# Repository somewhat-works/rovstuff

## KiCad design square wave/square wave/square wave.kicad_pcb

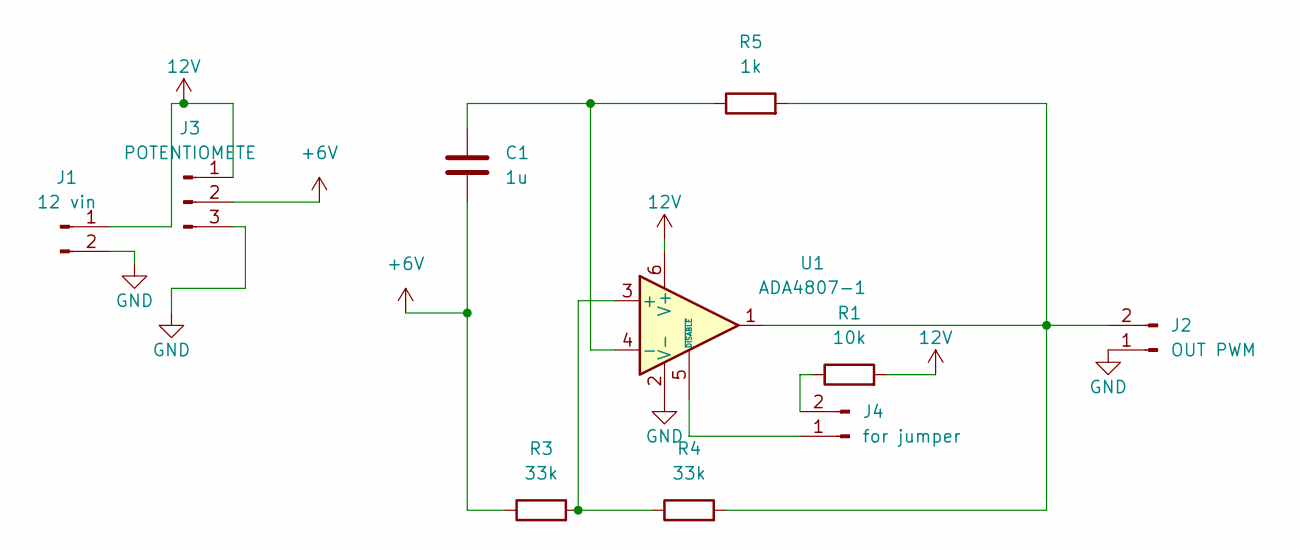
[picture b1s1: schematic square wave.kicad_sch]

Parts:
C1: 1u; C_0805_2012Metric
J1: 12 vin; PinHeader_1x02_P2.54mm_Vertical
J2: OUT PWM; PinHeader_1x02_P2.54mm_Vertical
J3: POTENTIOMETE; PinSocket_1x03_P2.54mm_Vertical
J4: for jumper; PinHeader_1x02_P2.54mm_Vertical
R1: 10k; R_0805_2012Metric
R3, R4: 33k; R_0805_2012Metric
R5: 1k; R_Axial_DIN0411_L9.9mm_D3.6mm_P15.24mm_Horizontal
U1: ADA4807-1; SOT-23-6

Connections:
12V: J1.1, J3.1, R1.2, U1.6 (V+)
+6V: C1.2, J3.2, R3.1
GND: J1.2, J2.1, J3.3, U1.2 (V-)
unnamed: J2.2, R4.2, R5.2, U1.1
unnamed: J4.1, U1.5 (~DISABLE)
unnamed: J4.2, R1.1
unnamed: R3.2, R4.1, U1.3 (+)
unnamed: C1.1, R5.1, U1.4 (-)

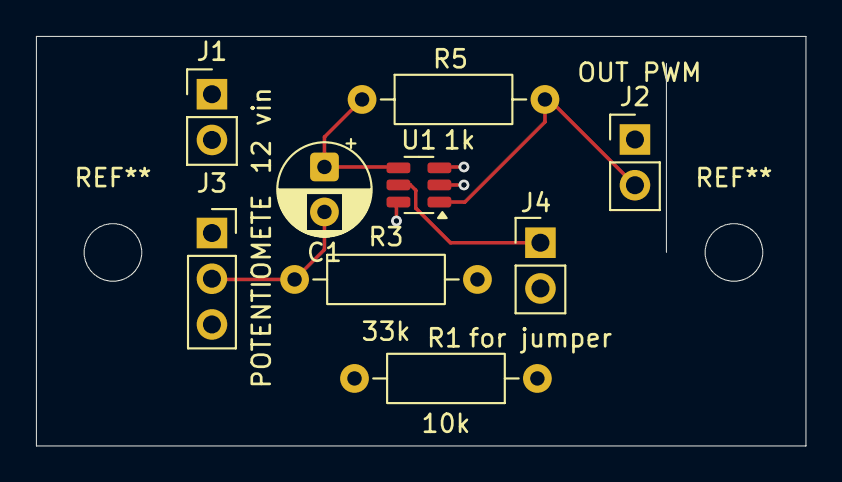
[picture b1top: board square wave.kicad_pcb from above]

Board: 4 copper layers, 42.8 x 22.8 mm, 9 parts (0 on the bottom side), 8 nets.

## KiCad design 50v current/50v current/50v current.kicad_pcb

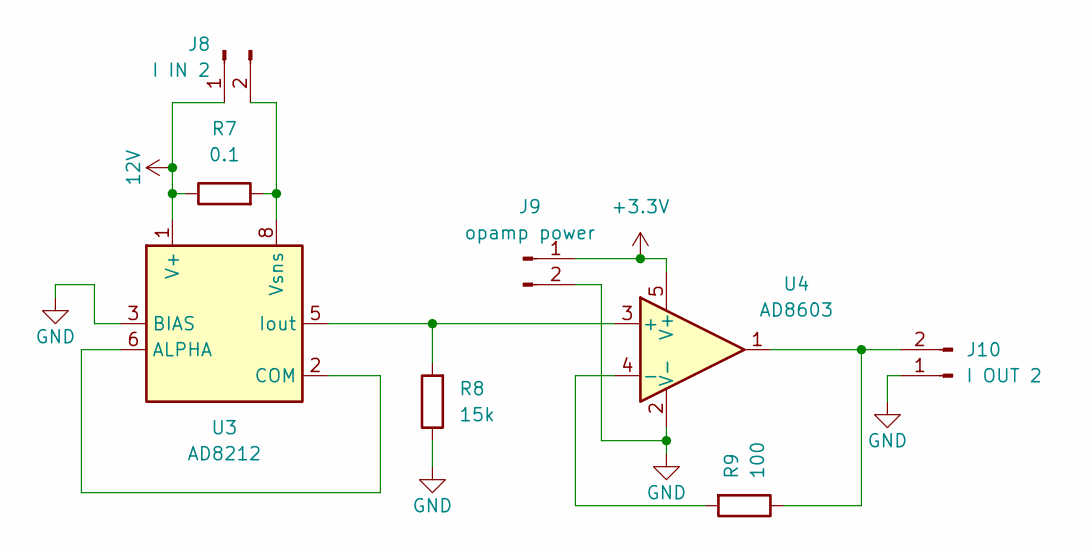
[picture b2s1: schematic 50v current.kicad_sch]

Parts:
J8: I IN 2; PinHeader_1x02_P2.54mm_Vertical
J9: opamp power; PinHeader_1x02_P2.54mm_Vertical
J10: I OUT 2; PinHeader_1x02_P2.54mm_Vertical
R7: 0.1; R_Axial_DIN0204_L3.6mm_D1.6mm_P5.08mm_Horizontal
R8: 15k; R_0805_2012Metric
R9: 100; R_0805_2012Metric
U3: AD8212; MSOP-8_3x3mm_P0.65mm
U4: AD8603; TSOT-23-5

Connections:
12V: J8.1, R7.1, U3.1 (V+)
+3.3V: J9.1, U4.5 (V+)
GND: J9.2, J10.1, R8.1, U3.3 (BIAS), U4.2 (V-)
unnamed: J8.2, R7.2, U3.8 (Vsns)
unnamed: J10.2, R9.1, U4.1
unnamed: U3.2 (COM), U3.6 (ALPHA)
unnamed: R8.2, U3.5 (Iout), U4.3 (+)
unnamed: R9.2, U4.4 (-)

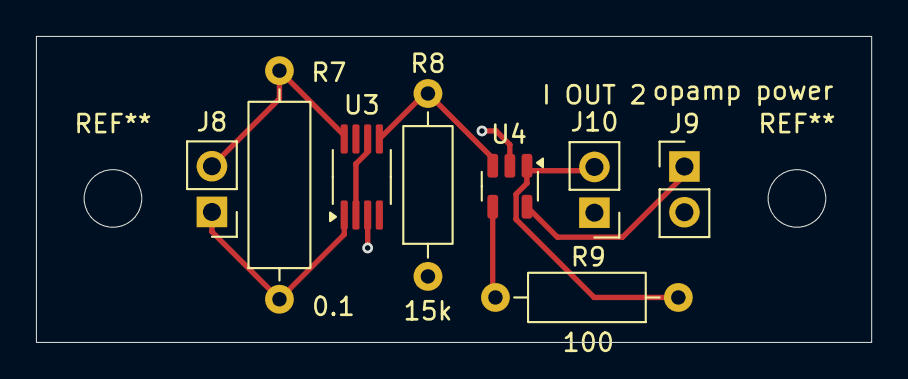
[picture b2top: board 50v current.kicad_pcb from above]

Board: 2 copper layers, 46.4 x 17.0 mm, 8 parts (0 on the bottom side), 8 nets.

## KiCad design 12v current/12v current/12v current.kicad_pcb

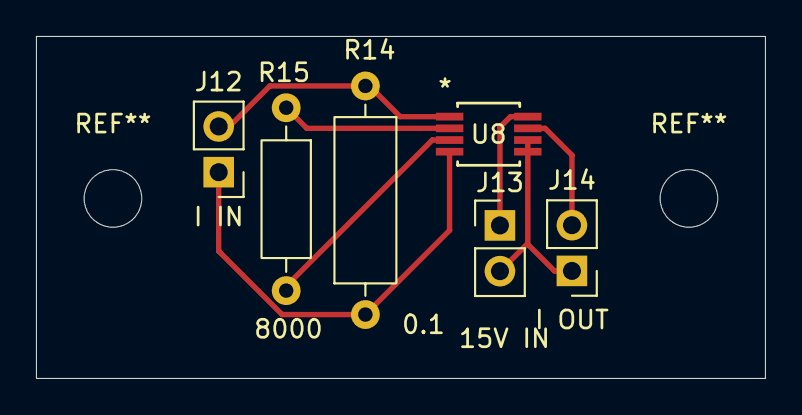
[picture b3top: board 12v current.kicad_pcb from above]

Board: 2 copper layers, 40.5 x 19.0 mm, 6 parts (0 on the bottom side), 7 nets.

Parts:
J12: I IN; PinHeader_1x02_P2.54mm_Vertical
J13: 15V IN; PinHeader_1x02_P2.54mm_Vertical
J14: I OUT; PinHeader_1x02_P2.54mm_Vertical
R14: 0.1; R_Axial_DIN0309_L9.0mm_D3.2mm_P12.70mm_Horizontal
R15: 8000; R_Axial_DIN0207_L6.3mm_D2.5mm_P10.16mm_Horizontal
U8: AD8227ARZ; RM_8_ADI

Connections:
12V: J12.1, R14.1, U8.4 (+IN)
+15V: J13.1, U8.8 (+VS)
GND: J13.2, J14.1, U8.5 (-VS), U8.6 (REF)
unnamed: J12.2, R14.2, U8.1 (-IN)
unnamed: J14.2, U8.7 (VOUT)
unnamed: R15.1, U8.2 (RG)
unnamed: R15.2, U8.3 (RG)

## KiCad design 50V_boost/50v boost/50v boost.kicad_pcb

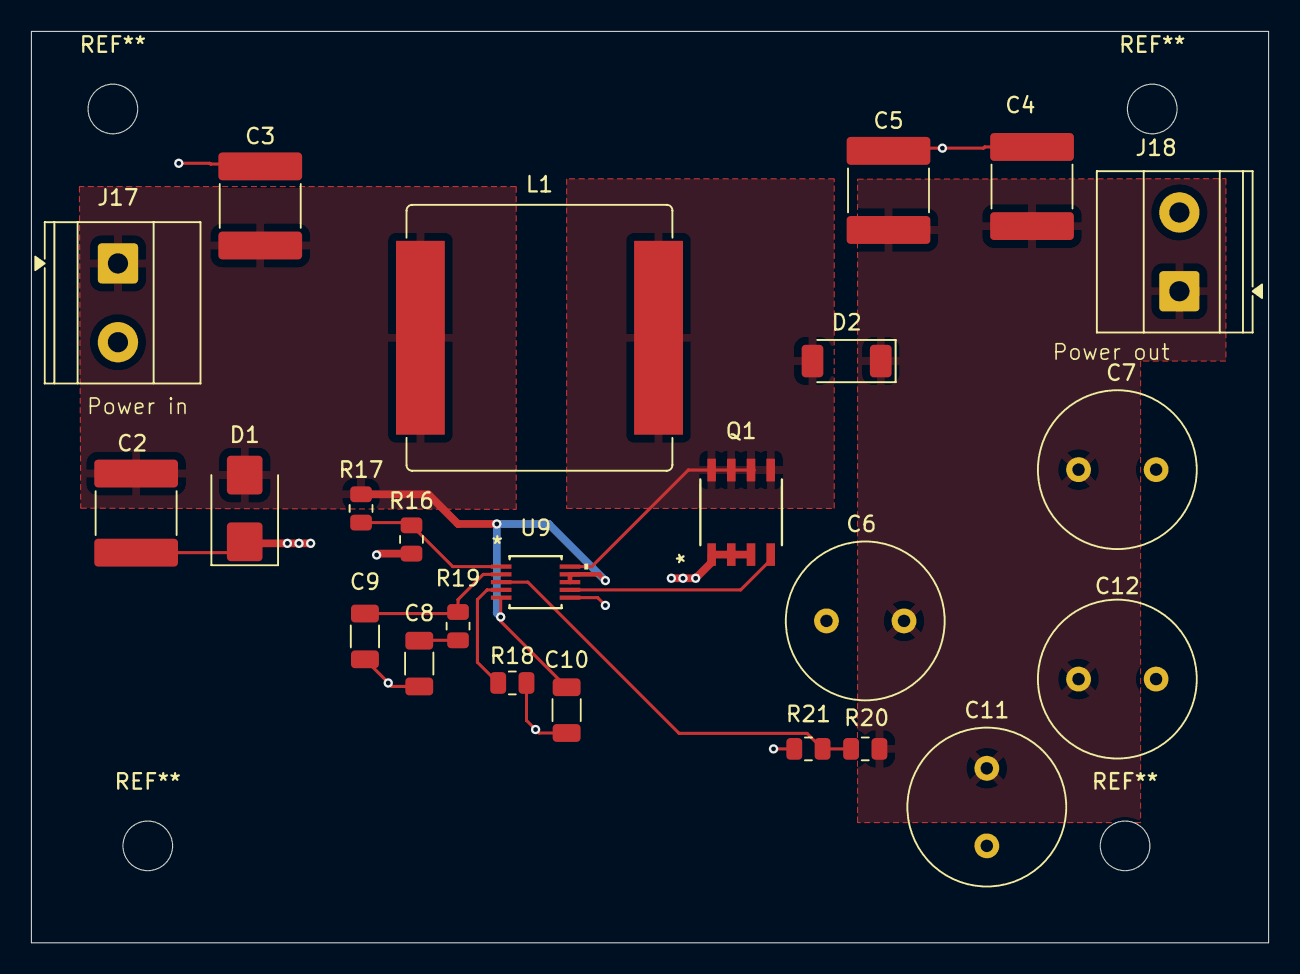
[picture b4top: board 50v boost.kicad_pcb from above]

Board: 2 copper layers, 79.8 x 58.8 mm, 24 parts (0 on the bottom side), 10 nets.

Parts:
C2, C3, C4, C5: 22u; C_2220_5750Metric
C6, C7, C11, C12: 100u; C_Radial_D10.0mm_H20.0mm_P5.00mm
C8: 6.8n; C_1206_3216Metric
C9: 47p; C_1206_3216Metric
C10: 4.7u; C_1206_3216Metric
D1: SMBJ24; D_SMB
D2: RB055LAM-60; D_SOD-128
J17, J18: Screw_Terminal_01x02; TerminalBlock_Phoenix_MKDS-1,5-2-5.08_1x02_P5.08mm_Horizont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
L1: SRP1770TA-150M; L_Bourns_SRP1770TA_16.9x16.9mm
Q1: IRF7805ZTRPBF; SO8_IRF7805_INF
R16, R21: 100k; R_0805_2012Metric
R17: 510k; R_0805_2012Metric
R18: 110k; R_0805_2012Metric
R19: 22k; R_0805_2012Metric
R20: 3.8Meg; R_0805_2012Metric
U9: LTC1871EMS-PBF; MSOP-10_MS_LIT

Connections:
/FB: R20.2, R21.1, U9.3 (FB)
/GATE: Q1.4, U9.7 (GATE)
/Ith: C9.1, R19.1, U9.2 (ITH)
/RUN: R16.1, R17.2, U9.1 (RUN)
/SENSE: D2.2 (A), L1.2, Q1.5, Q1.6, Q1.7, Q1.8, U9.10 (SENSE)
GND: C2.1, C3.2, C4.2, C5.2, C6.2, C7.2, C8.2, C9.2, C10.2, C11.2, C12.2, D1.1 (A1), J17.2, J18.2, Q1.1, Q1.2, Q1.3, R16.2, R18.2, R21.2, U9.6 (GND)
unnamed: C8.1, R19.2
unnamed: R18.1, U9.4 (FREQ)
VIN: C2.2, C3.1, C10.1, D1.2 (A2), J17.1, L1.1, R17.1, U9.5 (MODE/SYNC), U9.8 (INTVCC), U9.9 (VIN)
VOUT: C4.1, C5.1, C6.1, C7.1, C11.1, C12.1, D2.1 (K), J18.1, R20.1

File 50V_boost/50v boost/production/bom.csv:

Designator,Footprint,Quantity,Value,LCSC Part #
C10,1206,1,4.7u,
"C11, C12, C6, C7",C_Radial_D10.0mm_H20.0mm_P5.00mm,4,100u,
"C2, C3, C4, C5",2220,4,22u,
C8,1206,1,6.8n,
C9,1206,1,47p,
D1,D_SMB,1,SMBJ24,
D2,D_SOD-128,1,RB055LAM-60,
"J17, J18","TerminalBlock_Phoenix_MKDS-1,5-2-5.08_1x02_P5.08mm_Horizontal",2,Screw_Terminal_01x02,
L1,L_Bourns_SRP1770TA_16.9x16.9mm,1,SRP1770TA-150M,
Q1,SO8_IRF7805_INF,1,IRF7805ZTRPBF,
"R16, R21",0805,2,100k,
R17,0805,1,510k,
R18,0805,1,110k,
R19,0805,1,22k,
R20,0805,1,3.8Meg,
U9,MSOP-10_MS_LIT,1,LTC1871EMS-PBF,

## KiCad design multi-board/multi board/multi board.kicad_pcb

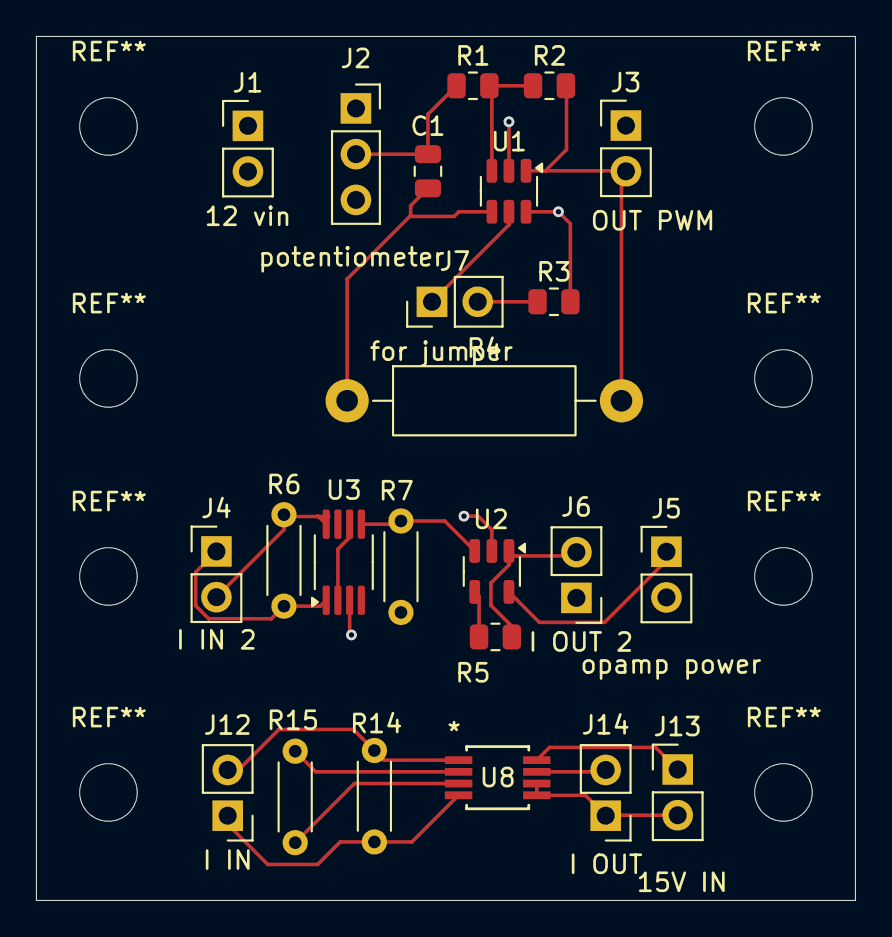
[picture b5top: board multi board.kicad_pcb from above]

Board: 4 copper layers, 45.5 x 48.0 mm, 24 parts (0 on the bottom side), 19 nets.

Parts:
C1: 1u; C_0805_2012Metric
J1: 12 vin; PinHeader_1x02_P2.54mm_Vertical
J2: potentiometer; PinSocket_1x03_P2.54mm_Vertical
J3: OUT PWM; PinHeader_1x02_P2.54mm_Vertical
J4: I IN 2; PinHeader_1x02_P2.54mm_Vertical
J5: opamp power; PinHeader_1x02_P2.54mm_Vertical
J6: I OUT 2; PinHeader_1x02_P2.54mm_Vertical
J7: for jumper; PinHeader_1x02_P2.54mm_Vertical
J12: I IN; PinHeader_1x02_P2.54mm_Vertical
J13: 15V IN; PinHeader_1x02_P2.54mm_Vertical
J14: I OUT; PinHeader_1x02_P2.54mm_Vertical
R1, R2: 33k; R_0805_2012Metric
R3: 10k; R_0805_2012Metric
R4: 1k; R_Axial_DIN0411_L9.9mm_D3.6mm_P15.24mm_Horizontal
R5: 100; R_0805_2012Metric
R6, R14: 0.1; R_Axial_DIN0204_L3.6mm_D1.6mm_P5.08mm_Horizontal
R7: 15k; R_Axial_DIN0204_L3.6mm_D1.6mm_P5.08mm_Horizontal
R15: 8000; R_Axial_DIN0204_L3.6mm_D1.6mm_P5.08mm_Horizontal
U1: ADA4807-1; SOT-23-6
U2: AD8603; TSOT-23-5
U3: AD8212; MSOP-8_3x3mm_P0.65mm
U8: AD8227ARZ; RM_8_ADI

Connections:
12V: J1.1, J2.1, J4.1, J12.1, R3.2, R6.1, R14.1, U1.6 (V+), U3.1 (V+), U8.4 (+IN)
+3.3V: J5.1, U2.5 (V+)
+6V: C1.2, J2.2, R1.1
+15V: J13.1, U8.8 (+VS)
GND: J1.2, J2.3, J3.1, J5.2, J6.1, J13.2, J14.1, R7.1, U1.2 (V-), U2.2 (V-), U3.3 (BIAS), U8.5 (-VS), U8.6 (REF)
unnamed: J3.2, R2.2, R4.2, U1.1
unnamed: J7.1, U1.5 (~DISABLE)
unnamed: J7.2, R3.1
unnamed: J12.2, R14.2, U8.1 (-IN)
unnamed: J14.2, U8.7 (VOUT)
unnamed: J4.2, R6.2, U3.8 (Vsns)
unnamed: J6.2, R5.1, U2.1
unnamed: R15.1, U8.2 (RG)
unnamed: R15.2, U8.3 (RG)
unnamed: R1.2, R2.1, U1.3 (+)
unnamed: C1.1, R4.1, U1.4 (-)
unnamed: U3.2 (COM), U3.6 (ALPHA)
unnamed: R7.2, U2.3 (+), U3.5 (Iout)
unnamed: R5.2, U2.4 (-)

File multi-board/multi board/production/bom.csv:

Designator,Footprint,Quantity,Value,LCSC Part #
C1,0805,1,1u,
J1,PinHeader_1x02_P2.54mm_Vertical,1,12 vin,
J12,PinHeader_1x02_P2.54mm_Vertical,1,I IN,
J13,PinHeader_1x02_P2.54mm_Vertical,1,15V IN,
J14,PinHeader_1x02_P2.54mm_Vertical,1,I OUT,
J2,PinSocket_1x03_P2.54mm_Vertical,1,potentiometer,
J3,PinHeader_1x02_P2.54mm_Vertical,1,OUT PWM,
J4,PinHeader_1x02_P2.54mm_Vertical,1,I IN 2,
J5,PinHeader_1x02_P2.54mm_Vertical,1,opamp power,
J6,PinHeader_1x02_P2.54mm_Vertical,1,I OUT 2,
J7,PinHeader_1x02_P2.54mm_Vertical,1,for jumper,
"R1, R2",0805,2,33k,
"R14, R6",R_Axial_DIN0204_L3.6mm_D1.6mm_P5.08mm_Horizontal,2,0.1,
R15,0805,1,8000,
R3,0805,1,10k,
R4,R_Axial_DIN0411_L9.9mm_D3.6mm_P15.24mm_Horizontal,1,1k,
R5,0805,1,100,
R7,0805,1,15k,
U1,SOT-23-6,1,ADA4807-1,
U2,TSOT-23-5,1,AD8603,
U3,MSOP-8_3x3mm_P0.65mm,1,AD8212,
U8,RM_8_ADI,1,AD8227ARZ,

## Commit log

2025-12-01 initial
